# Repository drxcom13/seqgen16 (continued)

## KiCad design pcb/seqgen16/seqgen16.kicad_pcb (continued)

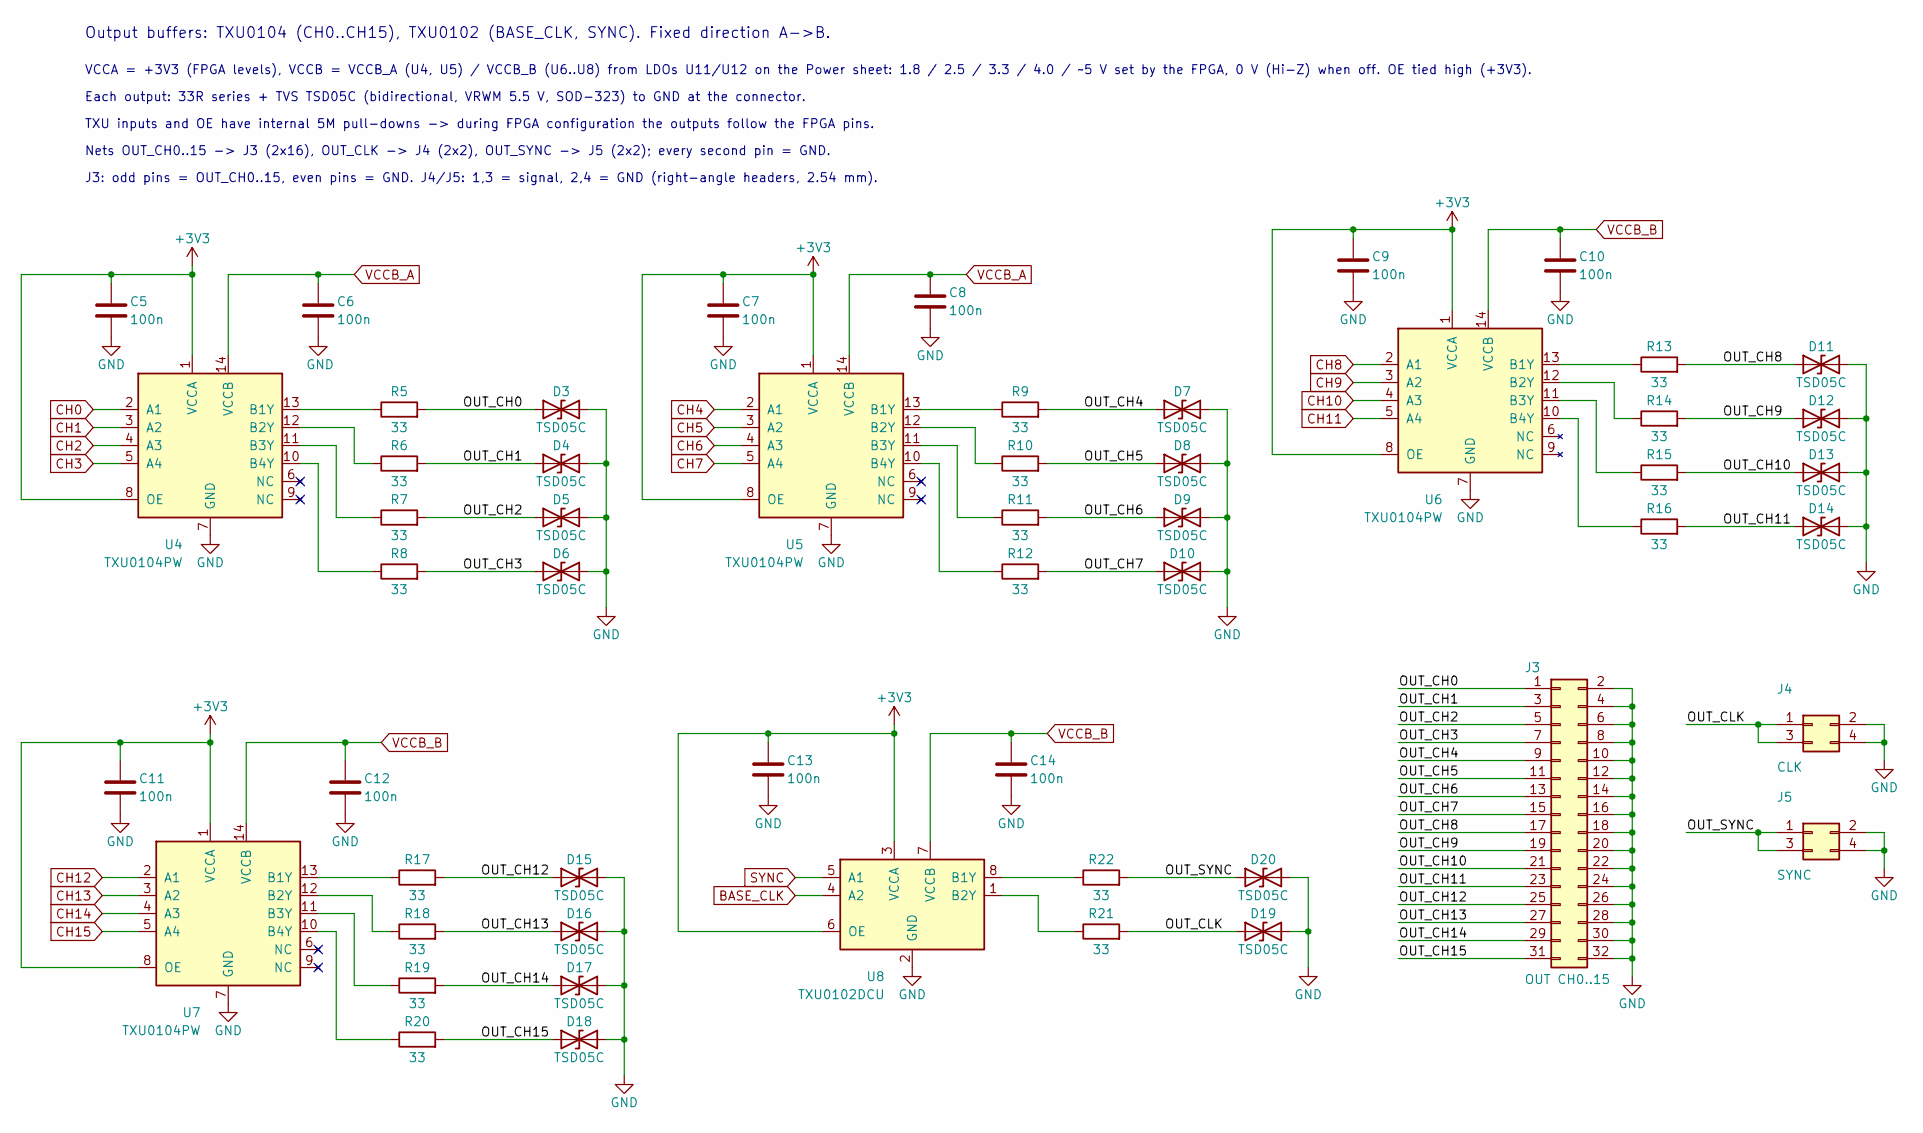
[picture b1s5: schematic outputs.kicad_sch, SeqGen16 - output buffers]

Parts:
C5, C6, C7, C8, C9, C10, C11, C12, C13, C14: 100n; C_0603_1608Metric
D3, D4, D5, D6, D7, D8, D9, D10, D11, D12, D13, D14, D15, D16, D17, D18, D19, D20: TSD05C; D_SOD-323
J3: OUT CH0..15; PinHeader_2x16_P2.54mm_Horizontal
J4: CLK; PinHeader_2x02_P2.54mm_Horizontal
J5: SYNC; PinHeader_2x02_P2.54mm_Horizontal
R5, R6, R7, R8, R9, R10, R11, R12, R13, R14, R15, R16, R17, R18, R19, R20, R21, R22: 33; R_0603_1608Metric
U4, U5, U6, U7: TXU0104PW; TSSOP-14_4.4x5mm_P0.65mm
U8: TXU0102DCU; VSSOP-8_2.3x2mm_P0.5mm

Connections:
+3V3: C5.1, C7.1, C9.1, C11.1, C13.1, U4.1 (VCCA), U4.8 (OE), U5.1 (VCCA), U5.8 (OE), U6.1 (VCCA), U6.8 (OE), U7.1 (VCCA), U7.8 (OE), U8.3 (VCCA), U8.6 (OE); also elsewhere on the board
/Outputs/OUT_CH0: D3.1 (A1), J3.1, R5.2
/Outputs/OUT_CH1: D4.1 (A1), J3.3, R6.2
/Outputs/OUT_CH2: D5.1 (A1), J3.5, R7.2
/Outputs/OUT_CH3: D6.1 (A1), J3.7, R8.2
/Outputs/OUT_CH4: D7.1 (A1), J3.9, R9.2
/Outputs/OUT_CH5: D8.1 (A1), J3.11, R10.2
/Outputs/OUT_CH6: D9.1 (A1), J3.13, R11.2
/Outputs/OUT_CH7: D10.1 (A1), J3.15, R12.2
/Outputs/OUT_CH8: D11.1 (A1), J3.17, R13.2
/Outputs/OUT_CH9: D12.1 (A1), J3.19, R14.2
/Outputs/OUT_CH10: D13.1 (A1), J3.21, R15.2
/Outputs/OUT_CH11: D14.1 (A1), J3.23, R16.2
/Outputs/OUT_CH12: D15.1 (A1), J3.25, R17.2
/Outputs/OUT_CH13: D16.1 (A1), J3.27, R18.2
/Outputs/OUT_CH14: D17.1 (A1), J3.29, R19.2
/Outputs/OUT_CH15: D18.1 (A1), J3.31, R20.2
/Outputs/OUT_CLK: D19.1 (A1), J4.1, J4.3, R21.2
/Outputs/OUT_SYNC: D20.1 (A1), J5.1, J5.3, R22.2
BASE_CLK: U8.4 (A2); also elsewhere on the board
CH0: U4.2 (A1); also elsewhere on the board
CH1: U4.3 (A2); also elsewhere on the board
CH2: U4.4 (A3); also elsewhere on the board
CH3: U4.5 (A4); also elsewhere on the board
CH4: U5.2 (A1); also elsewhere on the board
CH5: U5.3 (A2); also elsewhere on the board
CH6: U5.4 (A3); also elsewhere on the board
CH7: U5.5 (A4); also elsewhere on the board
CH8: U6.2 (A1); also elsewhere on the board
CH9: U6.3 (A2); also elsewhere on the board
CH10: U6.4 (A3); also elsewhere on the board
CH11: U6.5 (A4); also elsewhere on the board
CH12: U7.2 (A1); also elsewhere on the board
CH13: U7.3 (A2); also elsewhere on the board
CH14: U7.4 (A3); also elsewhere on the board
CH15: U7.5 (A4); also elsewhere on the board
GND: C5.2, C6.2, C7.2, C8.2, C9.2, C10.2, C11.2, C12.2, C13.2, C14.2, D3.2 (A2), D4.2 (A2), D5.2 (A2), D6.2 (A2), D7.2 (A2), D8.2 (A2), D9.2 (A2), D10.2 (A2), D11.2 (A2), D12.2 (A2), D13.2 (A2), D14.2 (A2), D15.2 (A2), D16.2 (A2), D17.2 (A2), D18.2 (A2), D19.2 (A2), D20.2 (A2), J3.2, J3.4, J3.6, J3.8, J3.10, J3.12, J3.14, J3.16, J3.18, J3.20, J3.22, J3.24, J3.26, J3.28, J3.30, J3.32, J4.2, J4.4, J5.2, J5.4, U4.7 (GND), U5.7 (GND), U6.7 (GND), U7.7 (GND), U8.2 (GND); also elsewhere on the board
unnamed: R5.1, U4.13 (B1Y)
unnamed: R6.1, U4.12 (B2Y)
unnamed: R7.1, U4.11 (B3Y)
unnamed: R8.1, U4.10 (B4Y)
unnamed: R9.1, U5.13 (B1Y)
unnamed: R10.1, U5.12 (B2Y)
unnamed: R11.1, U5.11 (B3Y)
unnamed: R12.1, U5.10 (B4Y)
unnamed: R13.1, U6.13 (B1Y)
unnamed: R14.1, U6.12 (B2Y)
unnamed: R15.1, U6.11 (B3Y)
unnamed: R16.1, U6.10 (B4Y)
unnamed: R17.1, U7.13 (B1Y)
unnamed: R18.1, U7.12 (B2Y)
unnamed: R19.1, U7.11 (B3Y)
unnamed: R20.1, U7.10 (B4Y)
unnamed: R22.1, U8.8 (B1Y)
unnamed: R21.1, U8.1 (B2Y)
SYNC: U8.5 (A1); also elsewhere on the board
VCCB_A: C6.1, C8.1, U4.14 (VCCB), U5.14 (VCCB); also elsewhere on the board
VCCB_B: C10.1, C12.1, C14.1, U6.14 (VCCB), U7.14 (VCCB), U8.7 (VCCB); also elsewhere on the board

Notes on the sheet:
Output buffers: TXU0104 (CH0..CH15), TXU0102 (BASE_CLK, SYNC). Fixed direction A->B.
Nets OUT_CH0..15 -> J3 (2x16), OUT_CLK -> J4 (2x2), OUT_SYNC -> J5 (2x2); every second pin = GND.
VCCA = +3V3 (FPGA levels), VCCB = VCCB_A (U4, U5) / VCCB_B (U6..U8) from LDOs U11/U12 on the Power sheet: 1.8 / 2.5 / 3.3 / 4.0 / ~5 V set by the FPGA, 0 V (Hi-Z) when off. OE tied high (+3V3).
J3: odd pins = OUT_CH0..15, even pins = GND. J4/J5: 1,3 = signal, 2,4 = GND (right-angle headers, 2.54 mm).
Each output: 33R series + TVS TSD05C (bidirectional, VRWM 5.5 V, SOD-323) to GND at the connector.
TXU inputs and OE have internal 5M pull-downs -> during FPGA configuration the outputs follow the FPGA pins.

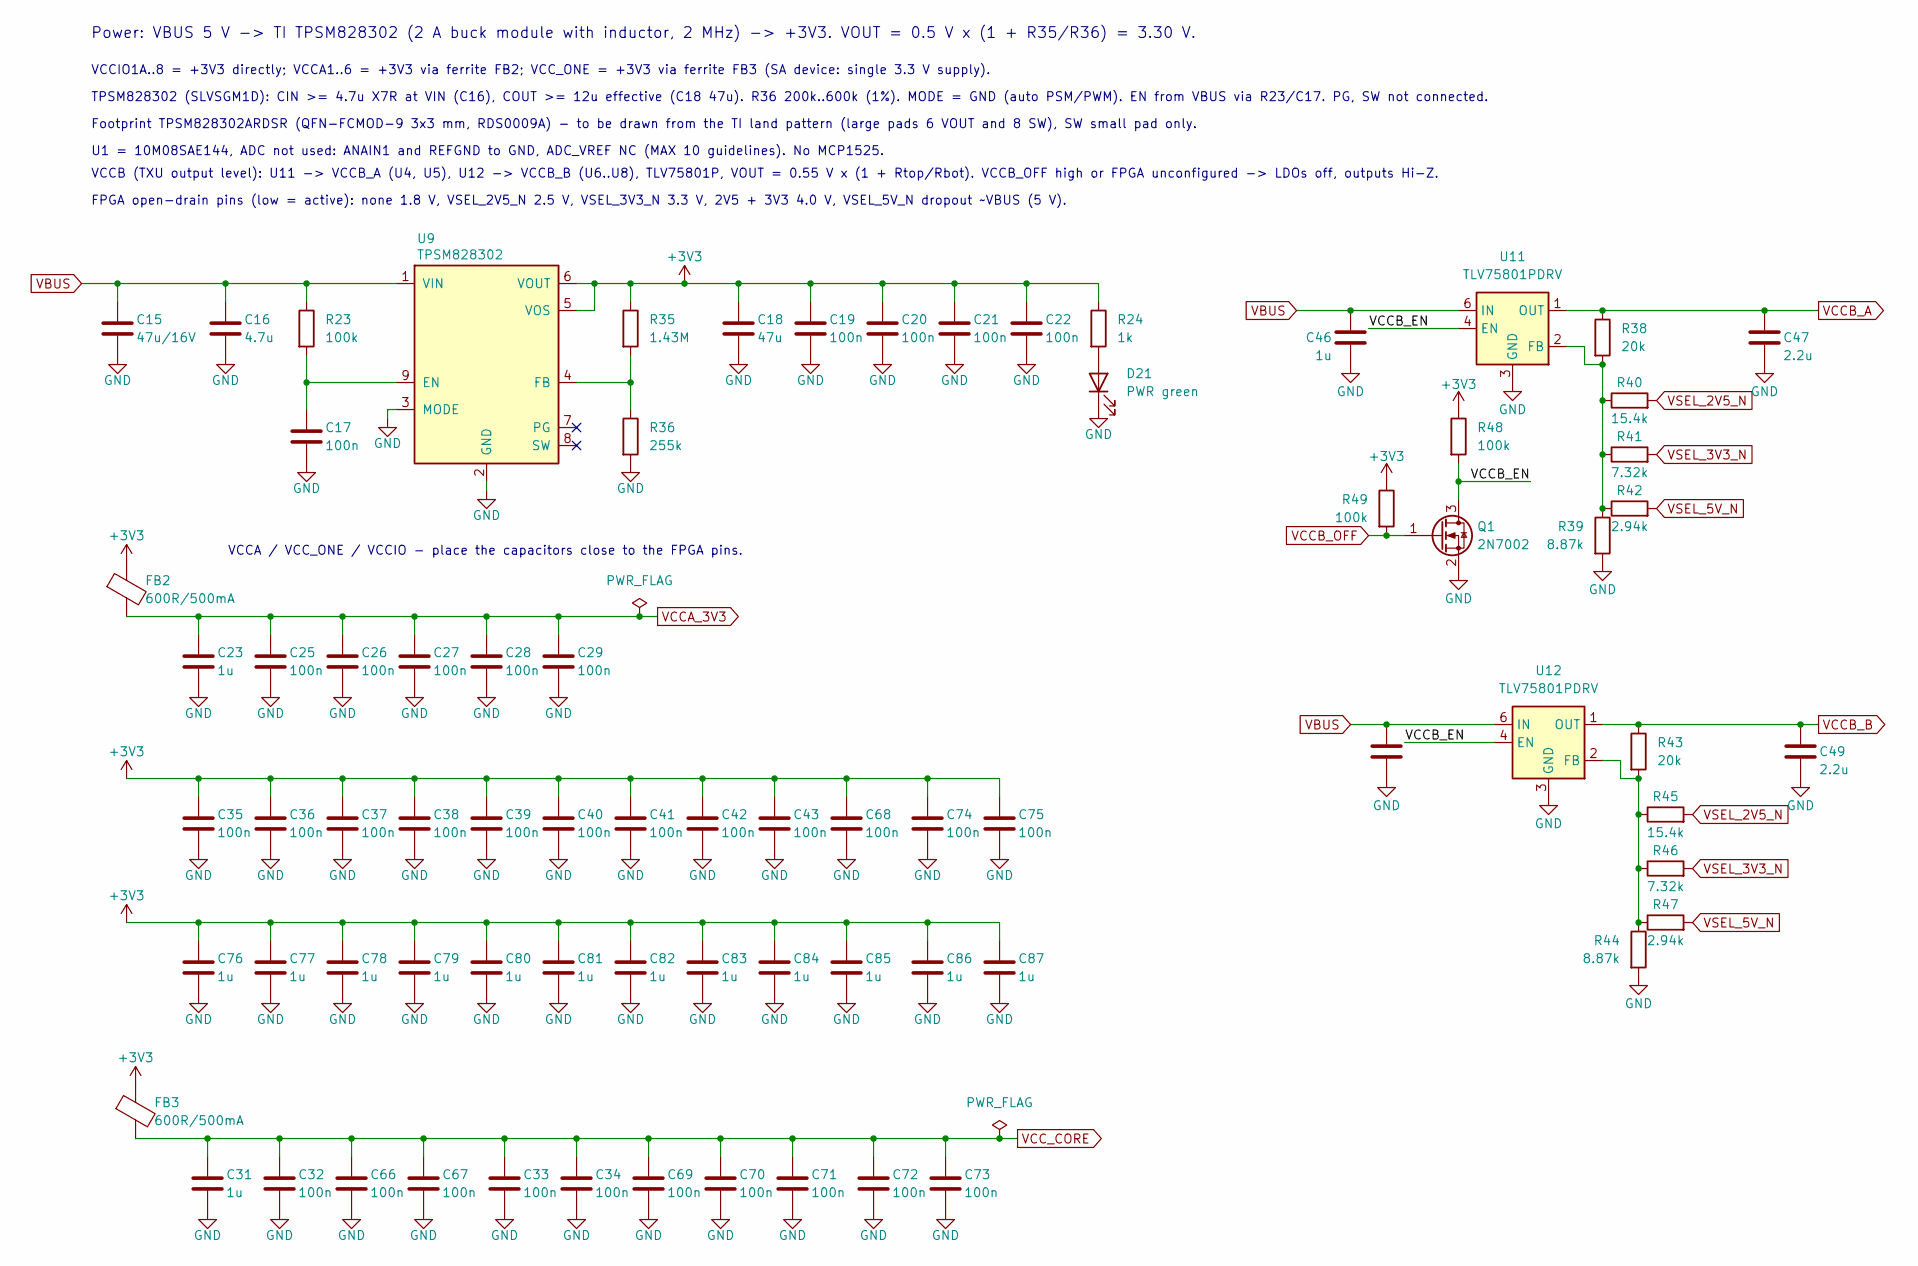
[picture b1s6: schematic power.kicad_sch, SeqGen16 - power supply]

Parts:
C15: 47u/16V; C_1206_3216Metric
C16: 4.7u; C_0603_1608Metric
C17, C19, C20, C21, C22, C25, C26, C27, C28, C29, C32, C33, C34, C35, C36, C37, C38, C39, C40, C41, C42, C43, C66, C67, C68, C69, C70, C71, C72, C73, C74, C75: 100n; C_0603_1608Metric
C18: 47u; C_0805_2012Metric
C23, C31, C46, C48, C76, C77, C78, C79, C80, C81, C82, C83, C84, C85, C86, C87: 1u; C_0603_1608Metric
C47, C49: 2.2u; C_0603_1608Metric
D21: PWR green; LED_0603_1608Metric
FB2, FB3: 600R/500mA; L_0603_1608Metric
Q1: 2N7002; SOT-23
R23, R48, R49: 100k; R_0603_1608Metric
R24: 1k; R_0603_1608Metric
R35: 1.43M; R_0603_1608Metric
R36: 255k; R_0603_1608Metric
R38, R43: 20k; R_0603_1608Metric
R39, R44: 8.87k; R_0603_1608Metric
R40, R45: 15.4k; R_0603_1608Metric
R41, R46: 7.32k; R_0603_1608Metric
R42, R47: 2.94k; R_0603_1608Metric
U9: TPSM828302; TI_RDS0009A_QFN-FCMOD-9_3x3mm
U11, U12: TLV75801PDRV; WSON-6-1EP_2x2mm_P0.65mm_EP1x1.6mm

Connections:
+3V3: C18.1, C19.1, C20.1, C21.1, C22.1, C35.1, C36.1, C37.1, C38.1, C39.1, C40.1, C41.1, C42.1, C43.1, C68.1, C74.1, C75.1, C76.1, C77.1, C78.1, C79.1, C80.1, C81.1, C82.1, C83.1, C84.1, C85.1, C86.1, C87.1, FB2.1, FB3.1, R24.1, R35.1, R48.1, R49.1, U9.5 (VOS), U9.6 (VOUT); also elsewhere on the board
/Power/VCCB_EN: Q1.3 (D), R48.2, U11.4 (EN), U12.4 (EN)
GND: C15.2, C16.2, C17.2, C18.2, C19.2, C20.2, C21.2, C22.2, C23.2, C25.2, C26.2, C27.2, C28.2, C29.2, C31.2, C32.2, C33.2, C34.2, C35.2, C36.2, C37.2, C38.2, C39.2, C40.2, C41.2, C42.2, C43.2, C46.2, C47.2, C48.2, C49.2, C66.2, C67.2, C68.2, C69.2, C70.2, C71.2, C72.2, C73.2, C74.2, C75.2, C76.2, C77.2, C78.2, C79.2, C80.2, C81.2, C82.2, C83.2, C84.2, C85.2, C86.2, C87.2, D21.1 (K), Q1.2 (S), R36.2, R39.2, R44.2, U9.2 (GND), U9.3 (MODE), U11.3 (GND), U11.7 (GND), U12.3 (GND), U12.7 (GND); also elsewhere on the board
unnamed: D21.2 (A), R24.2
unnamed: C17.1, R23.2, U9.9 (EN)
unnamed: R35.2, R36.1, U9.4 (FB)
unnamed: R38.2, R39.1, R40.1, R41.1, R42.1, U11.2 (FB)
unnamed: R43.2, R44.1, R45.1, R46.1, R47.1, U12.2 (FB)
VBUS: C15.1, C16.1, C46.1, C48.1, R23.1, U9.1 (VIN), U11.6 (IN), U12.6 (IN); also elsewhere on the board
VCCA_3V3: C23.1, C25.1, C26.1, C27.1, C28.1, C29.1, FB2.2; also elsewhere on the board
VCCB_A: C47.1, R38.1, U11.1 (OUT); also elsewhere on the board
VCCB_B: C49.1, R43.1, U12.1 (OUT); also elsewhere on the board
VCCB_OFF: Q1.1 (G), R49.2; also elsewhere on the board
VCC_CORE: C31.1, C32.1, C33.1, C34.1, C66.1, C67.1, C69.1, C70.1, C71.1, C72.1, C73.1, FB3.2; also elsewhere on the board
VSEL_2V5_N: R40.2, R45.2; also elsewhere on the board
VSEL_3V3_N: R41.2, R46.2; also elsewhere on the board
VSEL_5V_N: R42.2, R47.2; also elsewhere on the board

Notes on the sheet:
U1 = 10M08SAE144, ADC not used: ANAIN1 and REFGND to GND, ADC_VREF NC (MAX 10 guidelines). No MCP1525.
TPSM828302 (SLVSGM1D): CIN >= 4.7u X7R at VIN (C16), COUT >= 12u effective (C18 47u). R36 200k..600k (1%). MODE = GND (auto PSM/PWM). EN from VBUS via R23/C17. PG, SW not connected.
Footprint TPSM828302ARDSR (QFN-FCMOD-9 3x3 mm, RDS0009A) - to be drawn from the TI land pattern (large pads 6 VOUT and 8 SW), SW small pad only.
VCCIO1A..8 = +3V3 directly; VCCA1..6 = +3V3 via ferrite FB2; VCC_ONE = +3V3 via ferrite FB3 (SA device: single 3.3 V supply).
VCCA / VCC_ONE / VCCIO - place the capacitors close to the FPGA pins.
VCCB (TXU output level): U11 -> VCCB_A (U4, U5), U12 -> VCCB_B (U6..U8), TLV75801P, VOUT = 0.55 V x (1 + Rtop/Rbot). VCCB_OFF high or FPGA unconfigured -> LDOs off, outputs Hi-Z.
Power: VBUS 5 V -> TI TPSM828302 (2 A buck module with inductor, 2 MHz) -> +3V3. VOUT = 0.5 V x (1 + R35/R36) = 3.30 V.
FPGA open-drain pins (low = active): none 1.8 V, VSEL_2V5_N 2.5 V, VSEL_3V3_N 3.3 V, 2V5 + 3V3 4.0 V, VSEL_5V_N dropout ~VBUS (5 V).

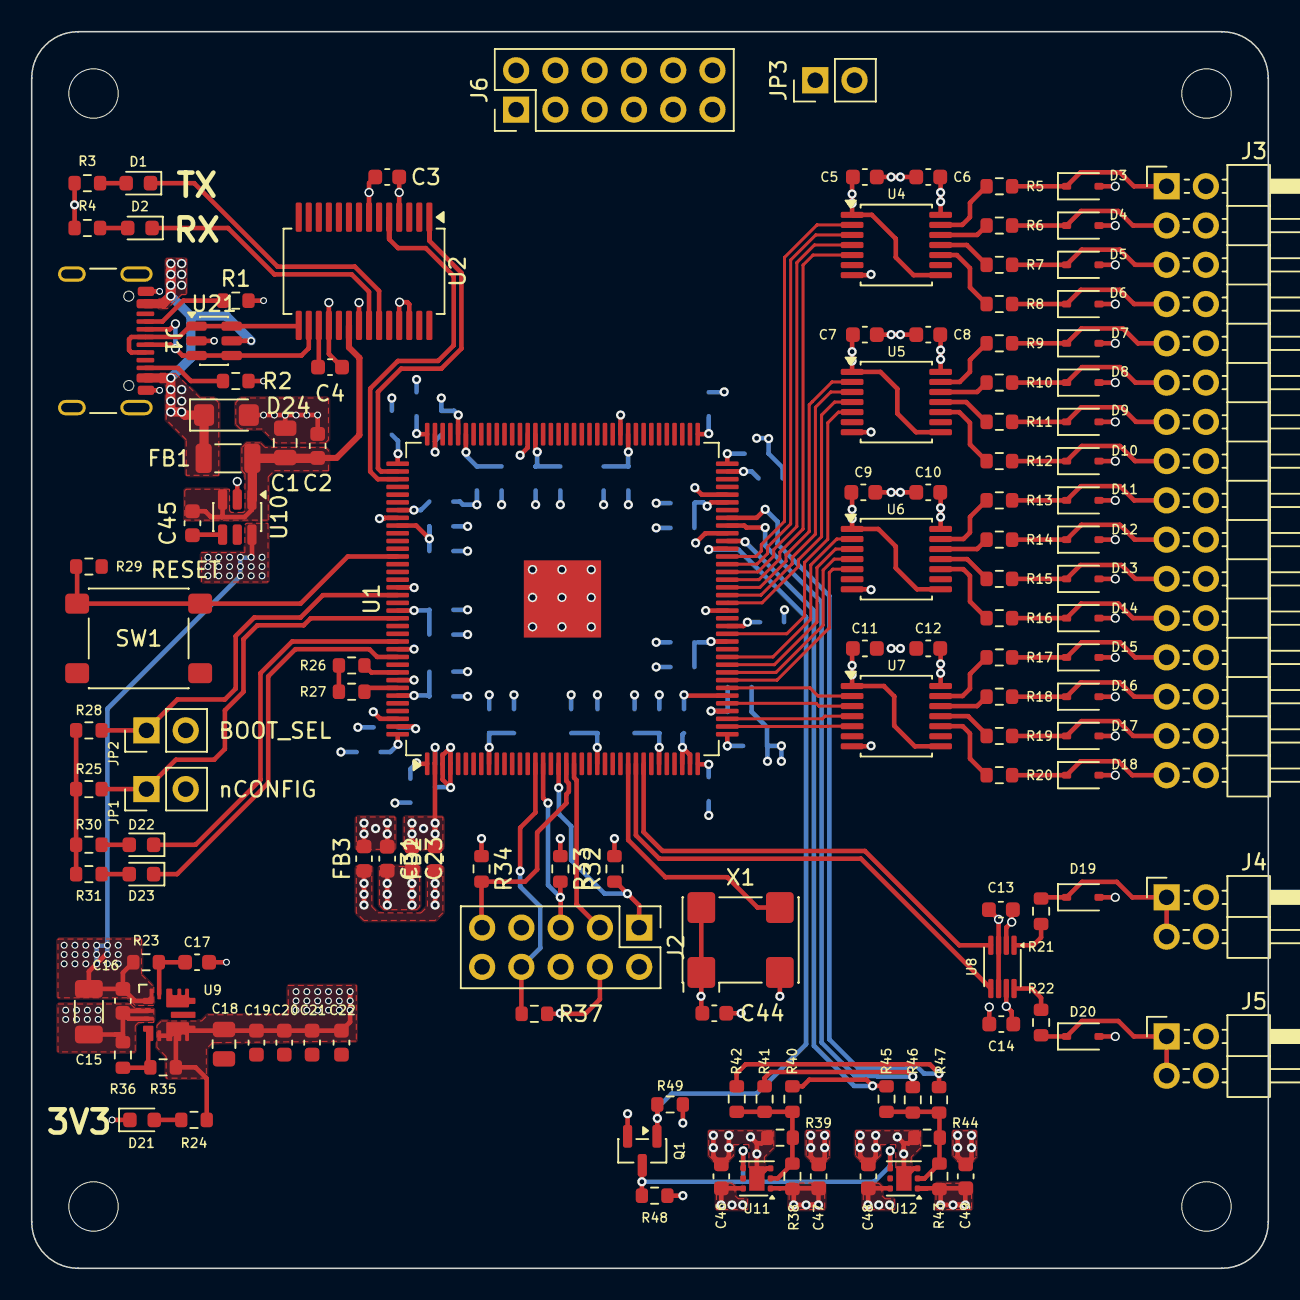
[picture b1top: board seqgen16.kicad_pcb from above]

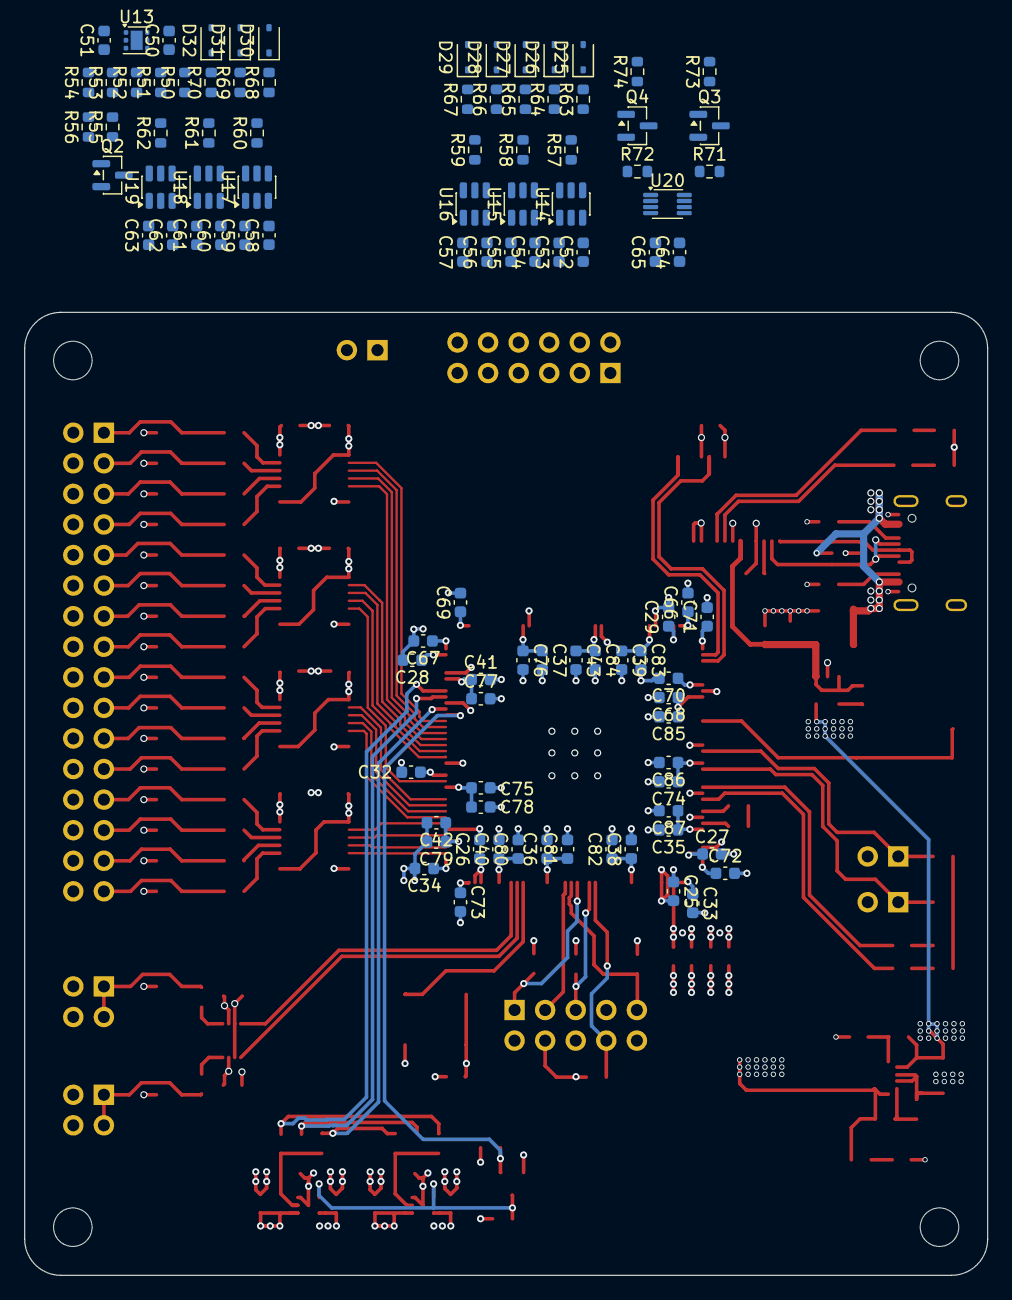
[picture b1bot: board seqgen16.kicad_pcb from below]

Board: 4 copper layers, 80.0 x 80.0 mm, 233 parts (99 on the bottom side), 137 nets.

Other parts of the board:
H1, H2, H3, H4: M3; MountingHole_3.2mm_M3

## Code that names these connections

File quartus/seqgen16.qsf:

set_global_assignment -name FAMILY "MAX 10"
set_global_assignment -name DEVICE 10M08SAE144C8G
set_global_assignment -name TOP_LEVEL_ENTITY seqgen16_top
set_global_assignment -name PROJECT_OUTPUT_DIRECTORY output_files
set_global_assignment -name ORIGINAL_QUARTUS_VERSION 25.1
set_global_assignment -name LAST_QUARTUS_VERSION "25.1std.0 SP0.02std Lite Edition"

set_global_assignment -name VHDL_FILE reset_ctrl.vhd
set_global_assignment -name VHDL_FILE seqgen16_top.vhd
set_global_assignment -name QIP_FILE nios_sys/synthesis/nios_sys.qip
set_global_assignment -name SDC_FILE seqgen16.sdc

# On-chip RAM Nios inicjalizowany z pliku -> wymagany tryb z inicjalizacja pamieci
set_global_assignment -name INTERNAL_FLASH_UPDATE_MODE "SINGLE IMAGE WITH ERAM"
set_global_assignment -name ON_CHIP_BITSTREAM_DECOMPRESSION OFF
set_global_assignment -name ENABLE_OCT_DONE OFF
set_global_assignment -name RESERVE_ALL_UNUSED_PINS_WEAK_PULLUP "AS INPUT TRI-STATED"
set_global_assignment -name STRATIX_DEVICE_IO_STANDARD "3.3-V LVCMOS"

# =============================================================================
# PINY - wlasna plytka pcb/seqgen16 (KiCad, etykiety globalne na U1 w fpga.kicad_sch)
# Przy zmianie pinow aktualizuj oba miejsca: ten plik i schemat.
# Poprzednie przypisanie dla MAX 10 10M08 Evaluation Kit: historia git (commit 22c6dcf).
# =============================================================================
set_location_assignment PIN_27  -to clk_50

# Przycisk RESET (SW1 na arkuszu Config, pull-up R29 1k), aktywny stanem niskim.
# Pin 121 = DEV_CLRn uzyty jako zwykle wejscie: device-wide reset musi byc wylaczony.
# Wewnetrzny pull-up - na plytce ewaluacyjnej pin moze byc niepodlaczony.
set_location_assignment PIN_121 -to reset_n
set_instance_assignment -name WEAK_PULL_UP_RESISTOR ON -to reset_n
set_global_assignment -name ENABLE_DEVICE_WIDE_RESET OFF

# LED (aktywne zerem). Na wlasnej plytce: LED1 = led_n[0] (pin 132, siec LED1_N), LED2 = led_n[1]
# (pin 134, LED2_N) - arkusz Config. led_n[2..4] (135/140/141) na plytce niepodlaczone, w FPGA na stale = 1 (wylaczone).
set_location_assignment PIN_132 -to led_n[0]
set_location_assignment PIN_134 -to led_n[1]
set_location_assignment PIN_135 -to led_n[2]
set_location_assignment PIN_140 -to led_n[3]
set_location_assignment PIN_141 -to led_n[4]

# UART (nazwy od strony FPGA): TXD -> RX mostka USB, RXD <- TX mostka USB (bank 7)
set_location_assignment PIN_111 -to uart_txd
set_location_assignment PIN_110 -to uart_rxd

# Kanaly 0..15 (bank 3), kolejnosc pinow malejaca = CH0 u gory J3 na plytce seqgen16
set_location_assignment PIN_60  -to ch_out[0]
set_location_assignment PIN_59  -to ch_out[1]
set_location_assignment PIN_58  -to ch_out[2]
set_location_assignment PIN_57  -to ch_out[3]
set_location_assignment PIN_56  -to ch_out[4]
set_location_assignment PIN_55  -to ch_out[5]
set_location_assignment PIN_54  -to ch_out[6]
set_location_assignment PIN_50  -to ch_out[7]
set_location_assignment PIN_47  -to ch_out[8]
set_location_assignment PIN_46  -to ch_out[9]
set_location_assignment PIN_45  -to ch_out[10]
set_location_assignment PIN_44  -to ch_out[11]
set_location_assignment PIN_43  -to ch_out[12]
set_location_assignment PIN_41  -to ch_out[13]
set_location_assignment PIN_39  -to ch_out[14]
set_location_assignment PIN_38  -to ch_out[15]

# Poziom wyjsc VCCB (arkusz Power: LDO U11/U12, Q1). vccb_off = 1 wylacza LDO.
# vsel_*_n open-drain do dzielnika FB LDO - bez pull-upow (prad pull-upu zmienilby napiecie).
set_location_assignment PIN_61  -to vccb_off
set_location_assignment PIN_62  -to vsel_2v5_n
set_location_assignment PIN_64  -to vsel_3v3_n
set_location_assignment PIN_65  -to vsel_5v_n
set_instance_assignment -name WEAK_PULL_UP_RESISTOR OFF -to vsel_2v5_n
set_instance_assignment -name WEAK_PULL_UP_RESISTOR OFF -to vsel_3v3_n
set_instance_assignment -name WEAK_PULL_UP_RESISTOR OFF -to vsel_5v_n

# Tester protokolow (zlacze J6, arkusz Protocol tester): banki 5 i 6
set_location_assignment PIN_80  -to pt_sck
set_location_assignment PIN_81  -to pt_mosi
set_location_assignment PIN_84  -to pt_cs
set_location_assignment PIN_85  -to pt_miso
set_location_assignment PIN_86  -to pt_dir_spi
set_location_assignment PIN_87  -to pt_dir_miso
set_location_assignment PIN_77  -to pt_tx
set_location_assignment PIN_79  -to pt_dir_tx
set_location_assignment PIN_98  -to pt_rx
set_location_assignment PIN_88  -to pt_sda_in
set_location_assignment PIN_89  -to pt_scl_in
set_location_assignment PIN_90  -to pt_sda_drv
set_location_assignment PIN_91  -to pt_scl_drv
# PVCC (LDO U13, Q2): jak VCCB - psel_*_n open-drain bez pull-upow
set_location_assignment PIN_92  -to pvcc_off
set_location_assignment PIN_93  -to psel_2v5_n
set_location_assignment PIN_96  -to psel_3v3_n
set_location_assignment PIN_97  -to psel_5v_n
set_instance_assignment -name WEAK_PULL_UP_RESISTOR OFF -to psel_2v5_n
set_instance_assignment -name WEAK_PULL_UP_RESISTOR OFF -to psel_3v3_n
set_instance_assignment -name WEAK_PULL_UP_RESISTOR OFF -to psel_5v_n

# SYNC i zegar bazowy na dwufunkcyjnych pinach zegarowych CLK1n/CLK1p (bank 2), uzyte jako wyjscia
set_location_assignment PIN_28  -to sync_out
set_location_assignment PIN_29  -to clk_base
set_instance_assignment -name SLEW_RATE 2 -to clk_base
set_instance_assignment -name SLEW_RATE 2 -to sync_out

# Ostatni rejestr kazdego wyjscia w komorce I/O -> minimalny rozrzut opoznien miedzy pinami
set_instance_assignment -name FAST_OUTPUT_REGISTER ON -to ch_out[*]
set_instance_assignment -name FAST_OUTPUT_REGISTER ON -to clk_base
set_instance_assignment -name FAST_OUTPUT_REGISTER ON -to sync_out

set_instance_assignment -name SLEW_RATE 2 -to ch_out[*]

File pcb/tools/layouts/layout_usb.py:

"""USB-UART sheet (usb.kicad_sch): USB-C J1 -> ESD U3 -> FT232RNL U2, supply filter, TX/RX LEDs."""
import os
import sys

sys.path.insert(0, os.path.join(os.path.dirname(os.path.abspath(__file__)), ".."))
from sch_build import Builder  # noqa: E402

RAIL = 73.66            # VBUS_USB -> FB1 -> VBUS


def build(path):
    b = Builder(path, paper="A4")
    P = b.pin

    # --- USB-C connector, CC pull-downs
    b.place("J1", 38.1, 101.6, fields={"Value": (38.1, 135.89, None)})
    b.place("R2", 63.5, 97.79)
    b.place("R1", 73.66, 97.79)
    b.wire(P("J1", "B5"), P("R2", "1"))                                    # CC2
    b.wire(P("J1", "A5"), (73.66, 91.44), P("R1", "1"))                    # CC1
    b.power("GND", P("R2", "2"))
    b.power("GND", P("R1", "2"))
    for p in ("A8", "B8"):
        b.nc(P("J1", p))
    b.wire(P("J1", "SH"), (30.48, 127), (60.96, 127))
    b.wire(P("J1", "A1"), (38.1, 127))
    b.power("GND", (38.1, 127))
    b.place("#FLG003", 60.96, 127, 0, {"Value": (60.96, 121.92, None)})

    # --- D-/D+ (pins A/B joined), one crossing because J1 has D- above D+
    b.wire(P("J1", "A7"), (58.42, 99.06))
    b.wire(P("J1", "B7"), (58.42, 101.6))
    b.wire((58.42, 99.06), (58.42, 111.76), (83.82, 111.76))
    b.wire(P("J1", "A6"), (55.88, 104.14))
    b.wire(P("J1", "B6"), (55.88, 106.68))
    b.wire((55.88, 104.14), (55.88, 109.22), (83.82, 109.22))

    # --- ESD protection (pins 1/6 and 3/4 are the same line -> named on both sides)
    b.place("U3", 88.9, 109.22)
    b.power("GND", P("U3", "2"))
    b.wire(P("U3", "6"), (121.92, 109.22))
    b.wire(P("U3", "4"), (121.92, 111.76))
    for x in (63.5, 101.6):
        b.label("USB_DP", (x, 109.22))
        b.label("USB_DM", (x, 111.76))

    # --- VBUS_USB (connector side) -> FB1 -> VBUS (whole board: FT232, buck, TXU VCCB)
    b.wire(P("J1", "A4"), (58.42, 86.36), (58.42, RAIL), (76.2, RAIL), (97.79, RAIL))
    b.label("VBUS_USB", (66.04, RAIL))
    b.place("D24", 76.2, RAIL + 3.81, 270, {"Reference": (78.74, 76.2, "left"),    # TVS SMF5.0A, cathode up
                                             "Value": (78.74, 78.74, "left")})
    b.power("GND", P("D24", "2"))
    b.wire(P("U3", "5"), (88.9, RAIL))
    b.place("#FLG004", 91.44, RAIL, 0, {"Value": (91.44, RAIL - 5.08, None)})
    b.place("FB1", 101.6, RAIL, 90)                                          # Wurth 74279221601 (1206, 2.5 A)
    b.place("C1", 116.84, RAIL + 3.81)
    b.place("C2", 127.0, RAIL + 3.81)
    b.place("#FLG012", 137.16, RAIL, 0, {"Value": (137.16, RAIL - 5.08, None)})
    # --- U10 TPS22917 load switch: VBUS_FT (FT232) -> soft-started VBUS (whole board); ON = VIN, C45 CT -> VIN
    b.place("U10", 167.64, 60.96, fields={"Reference": (167.64, 52.07, None), "Value": (167.64, 54.61, None)})
    b.place("C45", 153.67, 60.96, 90, {"Reference": (153.67, 53.34, None), "Value": (153.67, 55.88, None)})
    b.wire(P("FB1", "2"), (144.78, RAIL), (149.86, RAIL), (149.86, 63.5), (149.86, 60.96), (149.86, 58.42),
           P("U10", "1"))
    b.wire((149.86, 63.5), P("U10", "3"))
    b.label("VBUS_FT", (149.86, 71.12), "up")
    b.power("GND", P("U10", "2"))
    b.nc(P("U10", "5"))                                                     # QOD unused
    b.wire(P("U10", "6"), (187.96, 58.42))
    b.glabel("VBUS", (187.96, 58.42), "right")
    b.power("GND", P("C1", "2"))
    b.power("GND", P("C2", "2"))

    # --- FT232RNL
    b.place("U2", 142.24, 119.38)
    b.wire((144.78, RAIL), P("U2", "20"))                                   # VCC = VBUS
    b.wire(P("U2", "4"), (139.7, 81.28), (132.08, 81.28))                   # VCCIO = +3V3
    b.power("+3V3", (139.7, 81.28))
    b.place("C3", 132.08, 85.09)
    b.power("GND", P("C3", "2"))
    b.place("C4", 111.76, 101.6, 270, {"Reference": (111.76, 97.79, None),
                                       "Value": (113.03, 104.78, "left")})      # 3V3OUT decoupling
    b.wire(P("U2", "17"), P("C4", "1"))
    b.power("GND", P("C4", "2"))
    b.power("GND", P("U2", "26"))                                           # TEST
    for p in ("19", "27", "28", "2", "3", "6", "9", "10", "11", "12", "13", "14"):
        b.nc(P("U2", p))
    for p in ("25", "7", "18", "21"):
        x = P("U2", p)[0]
        b.wire(P("U2", p), (x, 147.32))
    b.wire((137.16, 147.32), (147.32, 147.32))
    b.power("GND", (142.24, 147.32))
    b.wire(P("U2", "1"), (165.1, 101.6))
    b.glabel("RXD", (165.1, 101.6), "right")
    b.wire(P("U2", "5"), (165.1, 104.14))
    b.glabel("TXD", (165.1, 104.14), "right")

    # --- TX / RX LEDs (CBUS0 / CBUS1 sink current)
    for led, res, x, pin in (("D1", "R3", 182.88, "23"), ("D2", "R4", 195.58, "22")):
        b.place(res, x, 102.87)
        b.place(led, x, 114.3, 90)
        b.power("+3V3", P(res, "1"))
        b.wire(P(res, "2"), P(led, "2"))
        y = P("U2", pin)[1]
        b.wire(P("U2", pin), (x, y), P(led, "1"))
    b.save()


if __name__ == "__main__":
    build(sys.argv[1])

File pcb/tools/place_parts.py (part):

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
# FPGA: rotated 90 CCW -> pins 37..72 (CH0..15, UART) face the output buffers on the right,
# pins 109..144 (configuration, LEDs, RESET) face the configuration block on the left,
# pins 1..36 (JTAG, CLK_50M, SYNC, BASE_CLK) face the bottom.
FX, FY = 34.0, 40.0
put("U1", FX, FY, 90)
# decoupling of VCCIO / VCCA / VCC_ONE on the bottom side, ring under the pin rows
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
# --- protocol tester (2026-11-25): J6 / JP3 on the top edge (front), SMD parts on the bottom side between
# J6 and the FPGA (banks 5/6 face the top edge). Keep x < 68.5 on the bottom: TVS vias of J3 at x = 69.25.
put("J6", 43.65, 5.4, 90)                       # odd pins (PVCC, SCK, MOSI, CS, SDA, TX) y = 5.4, even y = 2.86
put("JP3", 63.0, 3.5, 90)
for i, (d, r) in enumerate(zip(("D25", "D26", "D27", "D28", "D29", "D30", "D31", "D32"),
                               ("R63", "R64", "R65", "R66", "R67", "R68", "R69", "R70"))):
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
